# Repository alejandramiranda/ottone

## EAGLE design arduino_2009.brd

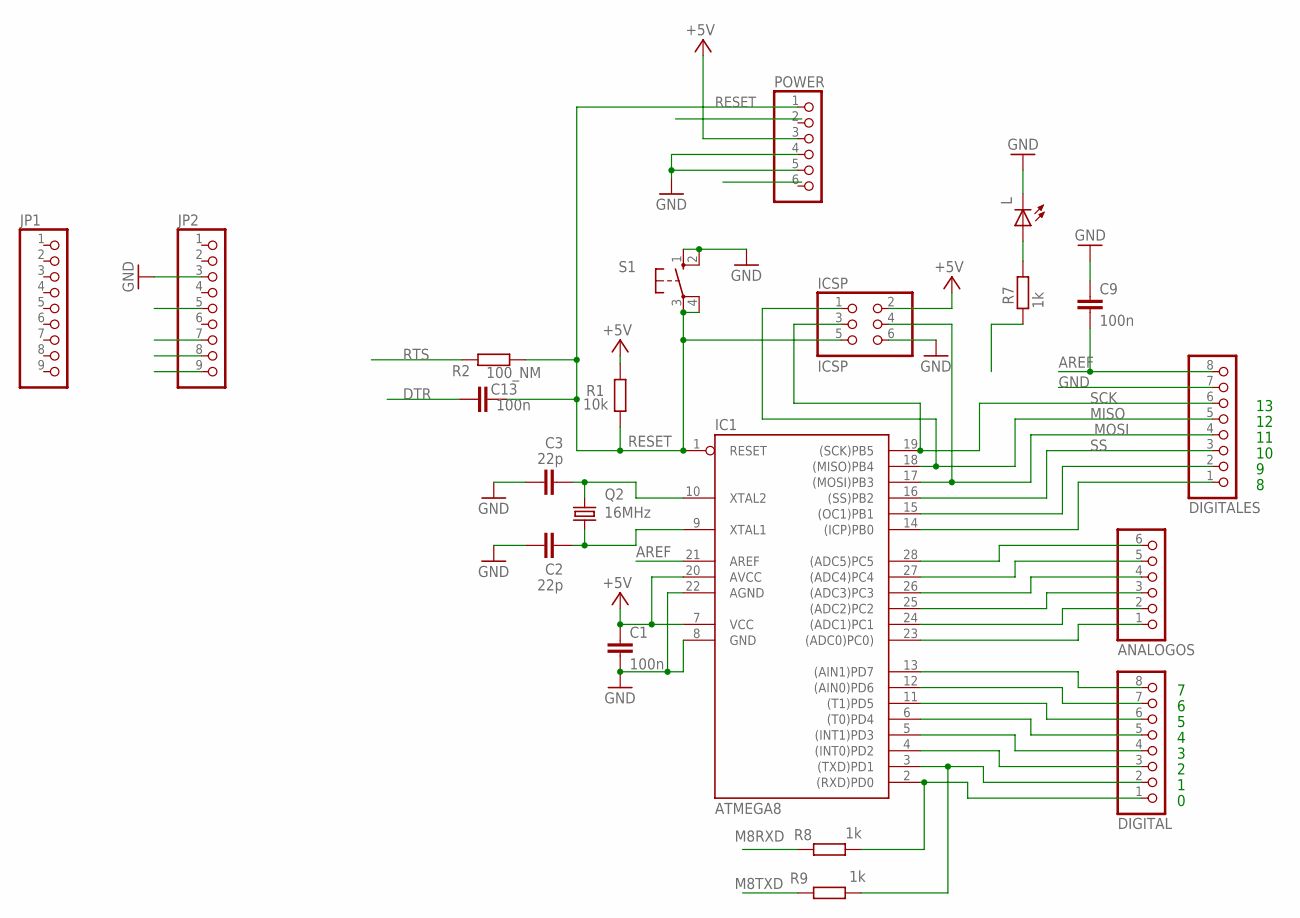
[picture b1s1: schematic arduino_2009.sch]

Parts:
ANALOGOS: PINHD-1X6; 1X06
C1, C9, C13: 100n; C2.5-3
C2, C3: 22p; C2.5-2
DIGITAL: PINHD-1X8; 1X08
DIGITALES: PINHD-1X8; 1X08
IC1: ATMEGA8; DIL28-3
ICSP: ICSP; 2X03
JP1, JP2: PINHD-1X9; 1X09
L: LED3MM
POWER: PINHD-1X6; 1X06
Q2: 16MHz; HC49/S
R1: 10k; 0204/5
R2: 100_NM; 0204/5
R7: 1k; 0207/7
R8, R9: 1k; 0204/5
S1: 10-XX; B3F-10XX

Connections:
+5V: C1.1, IC1.7 (VCC), IC1.20 (AVCC), ICSP.2, POWER.3, R1.2
AREF: C9.2, DIGITALES.8, IC1.21 (AREF)
DTR: C13.1, JP2.8
GND: C1.2, C2.1, C3.1, C9.1, DIGITALES.7, IC1.8 (GND), IC1.22 (AGND), ICSP.6, JP2.3, L.K (C), POWER.4, POWER.5, S1.1 (S), S1.2 (S1)
M8RXD: JP2.5, R8.2
M8TXD: JP2.9, R9.2
MISO: DIGITALES.5, IC1.18 ((MISO)PB4), ICSP.1
MOSI: DIGITALES.4, IC1.17 ((MOSI)PB3), ICSP.4
unnamed: L.A, R7.1
unnamed: DIGITALES.1, IC1.14 ((ICP)PB0)
unnamed: C2.2, IC1.9 (XTAL1), Q2.1
unnamed: C3.2, IC1.10 (XTAL2), Q2.2
unnamed: DIGITAL.3, IC1.4 ((INT0)PD2)
unnamed: DIGITAL.4, IC1.5 ((INT1)PD3)
unnamed: DIGITAL.5, IC1.6 ((T0)PD4)
unnamed: DIGITAL.6, IC1.11 ((T1)PD5)
unnamed: DIGITAL.7, IC1.12 ((AIN0)PD6)
unnamed: DIGITAL.8, IC1.13 ((AIN1)PD7), R7.2
unnamed: ANALOGOS.1, IC1.23 ((ADC0)PC0))
unnamed: ANALOGOS.2, IC1.24 ((ADC1)PC1)
unnamed: ANALOGOS.3, IC1.25 ((ADC2)PC2)
unnamed: ANALOGOS.4, IC1.26 ((ADC3)PC3)
unnamed: ANALOGOS.5, IC1.27 ((ADC4)PC4)
unnamed: ANALOGOS.6, IC1.28 ((ADC5)PC5)
unnamed: DIGITALES.2, IC1.15 ((OC1)PB1)
PD0: DIGITAL.1, IC1.2 ((RXD)PD0), R8.1
PD1: DIGITAL.2, IC1.3 ((TXD)PD1), R9.1
RESET: C13.2, IC1.1 (RESET), ICSP.5, POWER.1, R1.1, R2.2, S1.3, S1.4 (P1)
RTS: JP2.7, R2.1
SCK: DIGITALES.6, IC1.19 ((SCK)PB5), ICSP.3
SS: DIGITALES.3, IC1.16 ((SS)PB2)

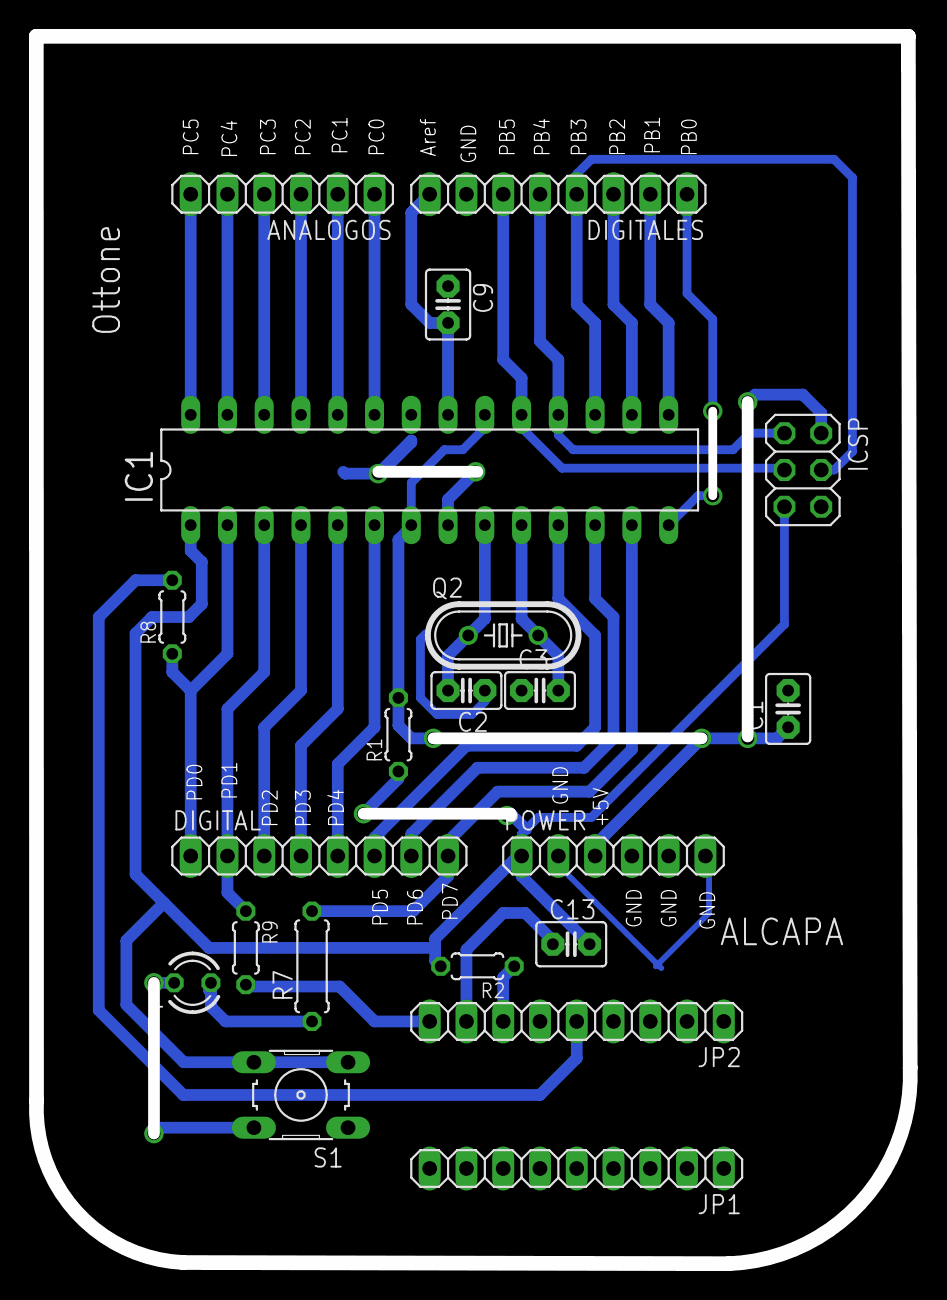
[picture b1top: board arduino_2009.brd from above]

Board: 2 copper layers, 60.4 x 84.8 mm, 21 parts (0 on the bottom side), 31 nets.

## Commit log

2017-02-17 diseño iniciql
2017-02-21 Creación del archivo package_index_json
2017-02-24 Creacion del esquematico y BRD de tarjeta Ottone
2017-02-24 Configuracion de Bootloaders
2017-02-24 v0.1.0
2017-03-10 Creacion de segunda version
2017-03-10 Tercera version
2017-03-10 Cuarta version
2017-04-07 Foto Placa Ottone
    Fotografía tomada al final del proceso, teniendo en cuenta las normas IEEE
